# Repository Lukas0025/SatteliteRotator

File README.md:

# Sattelite (antenna) Rotator (OpenSource and Open-source hardware) (HamLIB, Gpredict, satNOGS) (Linear motor EL)

Simple arduino antenna rotator with two axis (AZ and EL). For AZ is used step motor and for EL is used linear motor. 
For controll is created PCB with Arduino nano, step motor driver and four relays. Controller uses easycomm and rotator can work with HAM Lib, Gpredict, SatNOGS, ...

## Rotator setup

### Azimuth

For azimuth rotator can by used simply one gear on rope and step motor like here https://www.thingiverse.com/thing:4246844 or can by used some old HAM rotator and replace rotary pin with step motor.

* Step motor and rope

* Step motor and old rotator

### Elevation

For elevation is used linear motor more info is here https://www.qsl.net/sv1bsx/actuator/actuator.html

## Controller board

Board using Arduino Nano as microcontoler, A4988 for drive stepmotor, external 4 relay board for drive linear motor and same extesion ports. Board is designed in Kicad.

### Parts:

* Arduino Nano (https://www.ebay.com/itm/384943705316)
* A4988 Driver (https://www.ebay.com/itm/221921771119)
* 4 relay borad (4 channels) (https://www.ebay.com/itm/295078400027)
* 2x 100uF capacitator
* 2x 2 Pin 2.54mm Pitch PCB Screw Terminal Block (https://www.ebay.com/itm/264467271488)
* 2x 15pin 2.54mm Long Pin Female Header (https://www.ebay.com/itm/223478558792)
* 2x 8pin 2.54mm Long Pin Female Header (https://www.ebay.com/itm/223478558792)
* 1x 4pin 2.54mm Long Pin Male Header
* prited PCB 

### Extension ports

* Generic ports - 3 digitals and 2 analog ports
* SPI port
* I2C port
* power port - 5V, 3V3 and GND
* 2 relays

### Ports mapping

|  Boards          | Arduino Nano |
|------------------|--------------|
| Relay 1          |      D2      |
| Relay 2          |      D4      |
| Relay 3          |      D3      |
| Relay 4          |      D5      |
| Step Motor Step  |      D6      |
| Step Motor Dir   |      D7      |
| Generic 1        |      D8      |
| Generic 2        |      D9      |
| Generic 3        |      D10     |
| A0               |      A0      |
| A1               |      A1      |
| MI               |    MISO      |
| MO               |    MOSI      |
| SCK              |     SCK      |
| SDA (I2C)        |     SDA/A4   |
| SCL (I2C)        |     SCL/A5   |

## Connect with PC (HamLib, Gpredict, ...)

After code uploaded to arduino you need run rotctld for parse easycomm comunication.

```sh
sudo rotctld -m 202 -r /dev/ttyACM0 -s 9600 -T 127.0.0.1 -t 4533 -C timeout=5000 -C retry=0 -vvvvvvvv > pause
```

Connect to Gpredict using add rotator to Gpredict in Edit > Settings > Interface > Rotators > add new

then you can use rotator in Antenna controller

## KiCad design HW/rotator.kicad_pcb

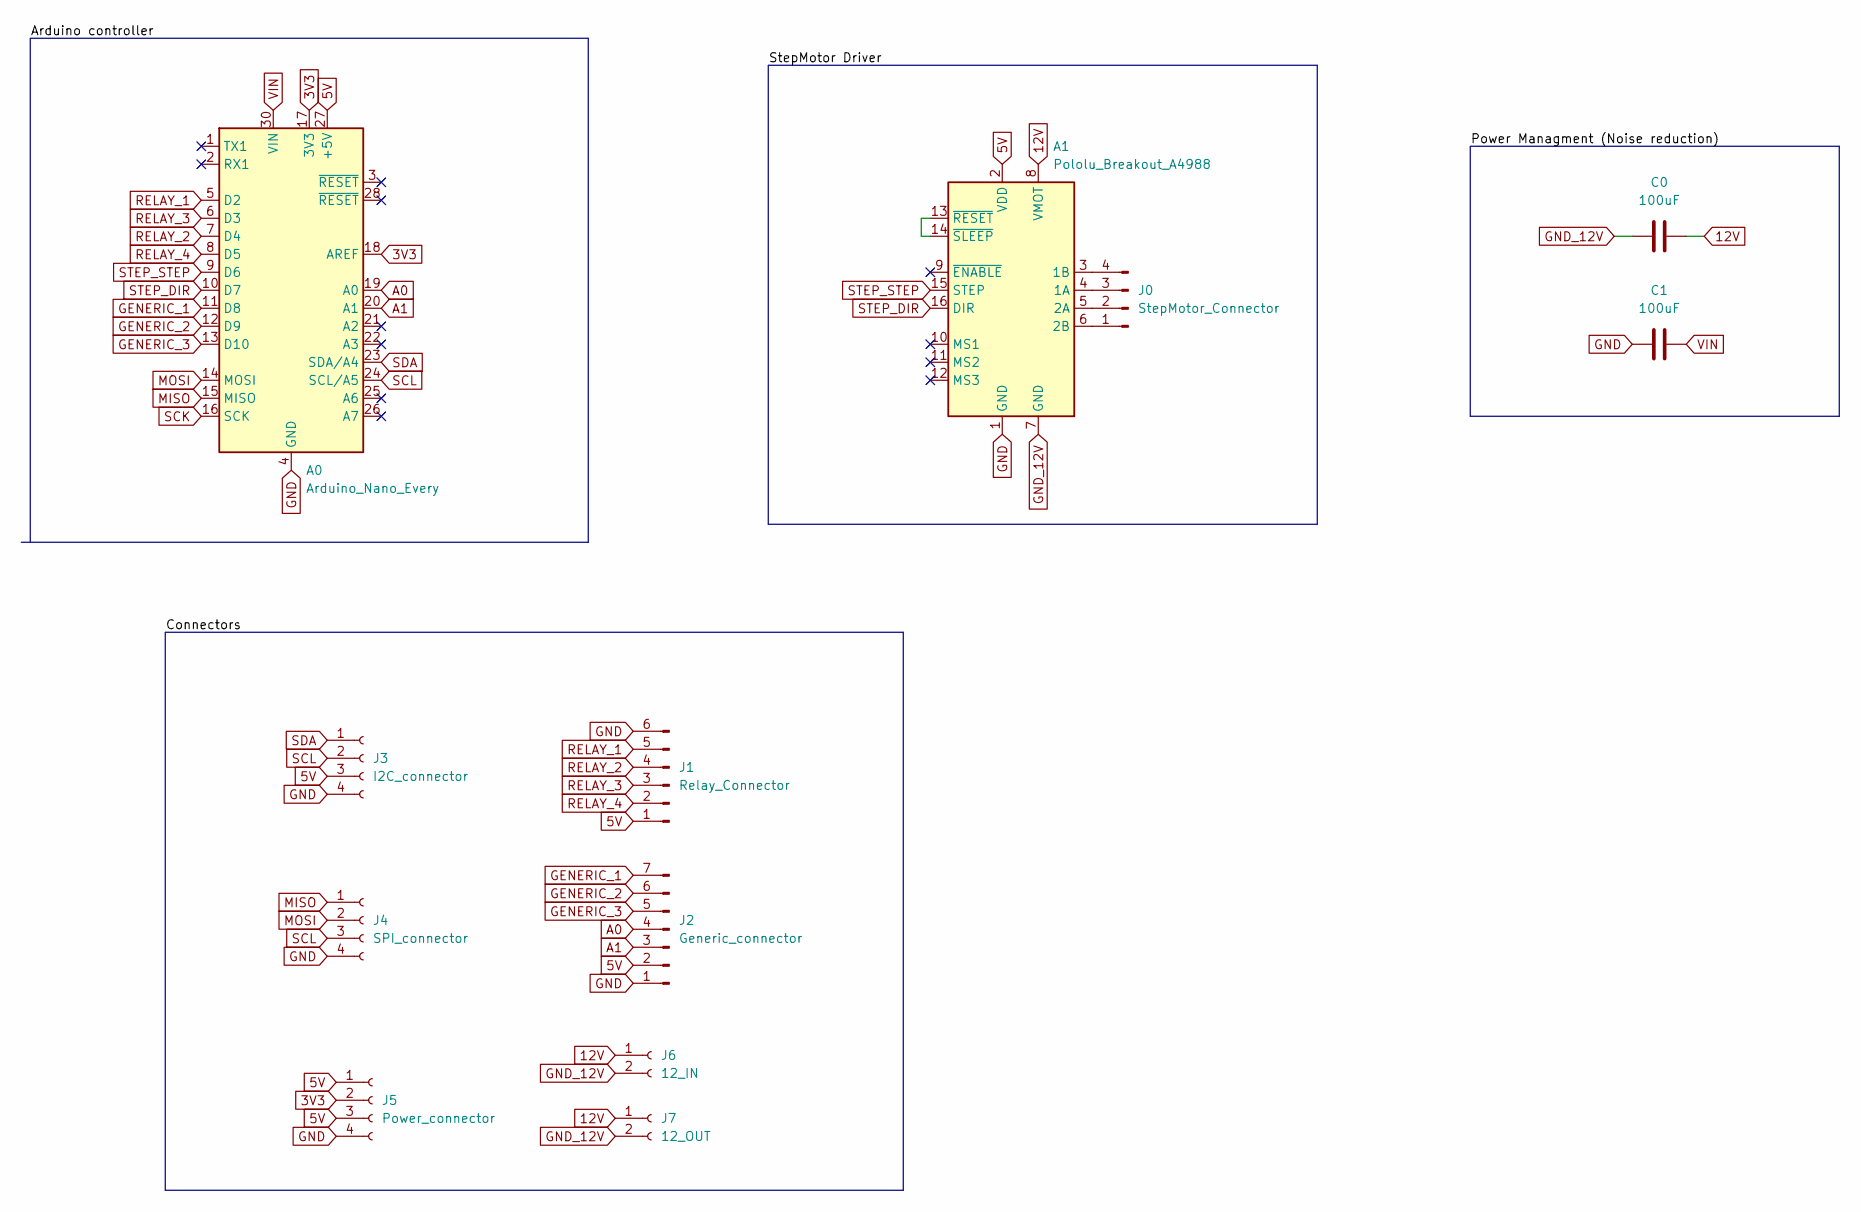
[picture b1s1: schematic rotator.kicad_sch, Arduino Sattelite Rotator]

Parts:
A0: Arduino_Nano_Every; Arduino_Nano
A1: Pololu_Breakout_A4988; Pololu_Breakout-16_15.2x20.3mm
C0, C1: 100uF; CP_Radial_D6.3mm_P2.50mm
J0: StepMotor_Connector; PinHeader_1x04_P2.54mm_Vertical
J1: Relay_Connector; PinHeader_1x06_P2.54mm_Vertical
J2: Generic_connector; PinHeader_1x07_P2.54mm_Vertical
J3: I2C_connector; PinHeader_1x04_P2.54mm_Vertical
J4: SPI_connector; PinHeader_1x04_P2.54mm_Vertical
J5: Power_connector; PinHeader_1x04_P2.54mm_Vertical
J6: 12_IN; PinHeader_1x02_P2.54mm_Vertical
J7: 12_OUT; PinHeader_1x02_P2.54mm_Vertical

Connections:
3V3: A0.17 (3V3), A0.18 (AREF), J5.2
5V: A0.27 (+5V), A1.2 (VDD), J1.1, J2.2, J3.3, J5.1, J5.3
12V: A1.8 (VMOT), C0.1, J6.1, J7.1
A0: A0.19 (A0), J2.4
A1: A0.20 (A1), J2.3
GENERIC_1: A0.11 (D8), J2.7
GENERIC_2: A0.12 (D9), J2.6
GENERIC_3: A0.13 (D10), J2.5
GND: A0.4 (GND), A0.29 (GND), A1.1 (GND), C1.2, J1.6, J2.1, J3.4, J4.4, J5.4
GND_12V: A1.7 (GND), C0.2, J6.2, J7.2
MISO: A0.15 (MISO), J4.1
MOSI: A0.14 (MOSI), J4.2
unnamed: A1.3 (1B), J0.4
unnamed: A1.4 (1A), J0.3
unnamed: A1.5 (2A), J0.2
unnamed: A1.6 (2B), J0.1
unnamed: A1.13 (~RESET), A1.14 (~SLEEP)
RELAY_1: A0.5 (D2), J1.5
RELAY_2: A0.7 (D4), J1.4
RELAY_3: A0.6 (D3), J1.3
RELAY_4: A0.8 (D5), J1.2
SCK: A0.16 (SCK)
SCL: A0.24 (SCL/A5), J3.2, J4.3
SDA: A0.23 (SDA/A4), J3.1
STEP_DIR: A0.10 (D7), A1.16 (DIR)
STEP_STEP: A0.9 (D6), A1.15 (STEP)
VIN: A0.30 (VIN), C1.1

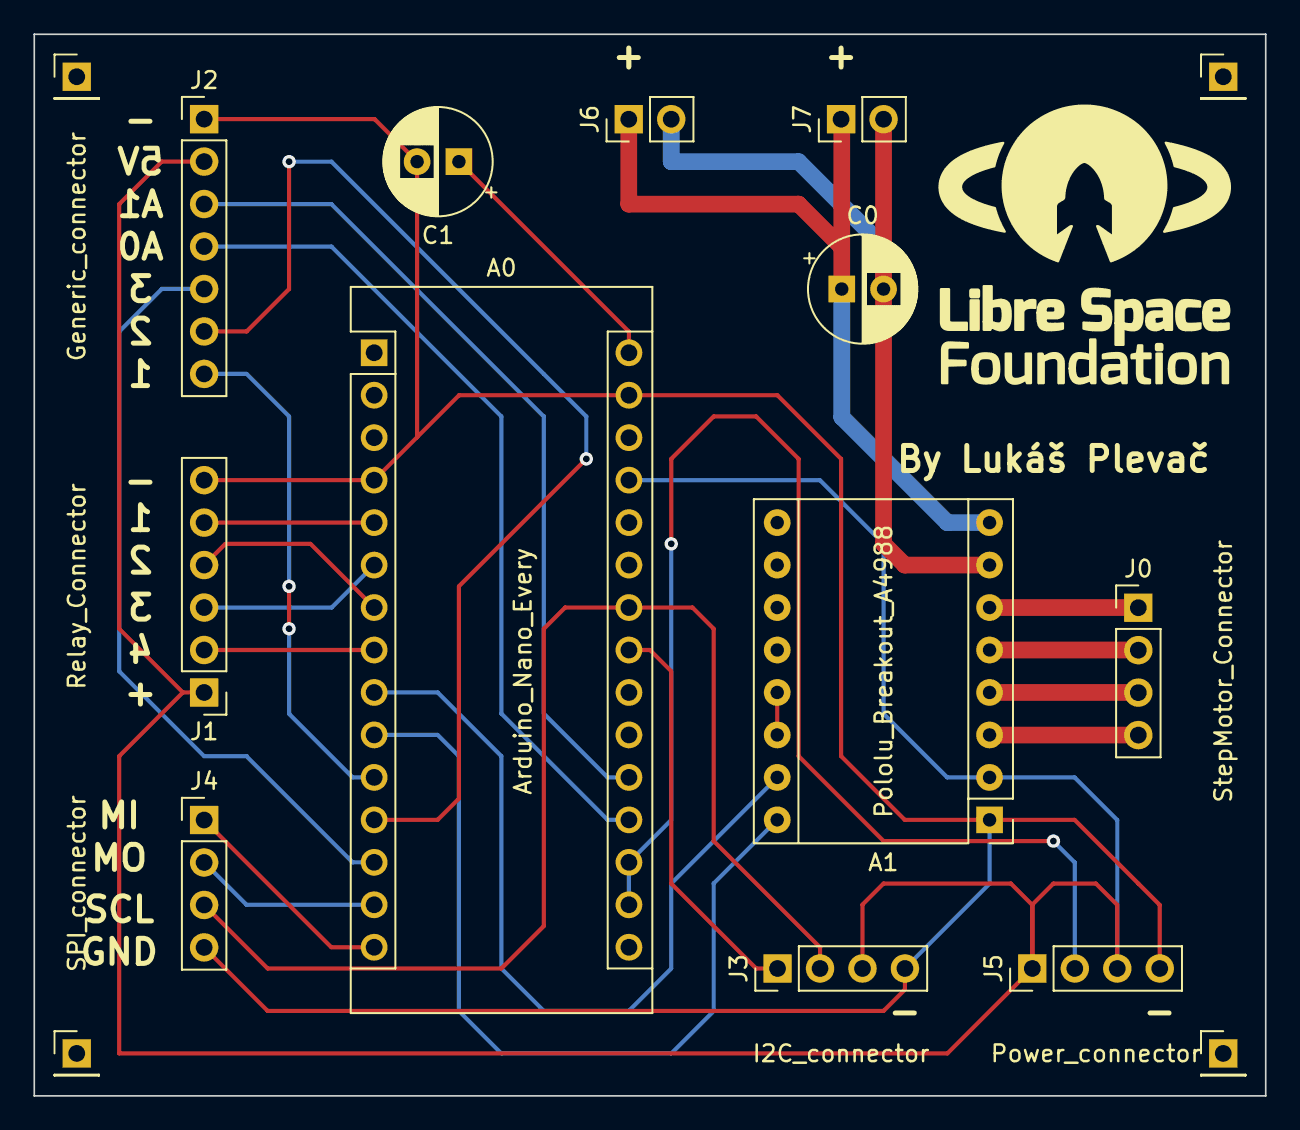
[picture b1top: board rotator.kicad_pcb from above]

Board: 2 copper layers, 73.7 x 63.5 mm, 12 parts (0 on the bottom side), 26 nets.

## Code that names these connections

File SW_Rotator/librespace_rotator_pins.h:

#pragma once

#include <Arduino.h>

#define RELAY_1 2
#define RELAY_2 4
#define RELAY_3 3
#define RELAY_4 5

#define GPIO_1 8
#define GPIO_2 9
#define GPIO_3 10

#define A_0 A0
#define A_1 A1

#define MI 12
#define MO 11
#define SCK 13
#define SDA A4
#define SCL A5

#define MOTOR_DIR 7
#define MOTOR_STEP 6

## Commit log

2022-07-06 Added HW and basic documenation
2022-07-06 Fixed readme
2022-07-06 Images resize
2022-07-06 Image resize
2022-07-06 Added testing code
2022-07-06 Added gerber
2022-07-06 Added pdf schematic
2022-07-06 Added ports mapping
2022-07-06 added info about I2C
2022-07-06 Added info to design
2022-07-06 Added design images
2022-07-06 Fixing readme img
2022-07-07 Added connectors
2022-07-16 Use macros for constants
2022-07-21 Fixed C1 polarization in DPS
2022-07-21 Update DPS design image with fixed polarization
2022-07-22 Added pins map header file
2022-07-22 FIxed exact timing
2022-08-01 Fixed capacitator C0 polarization
2022-08-01 Fixing ports mishmash
2022-10-18 Added restart conters for auto home after some degrees
2022-10-18 Overformated
